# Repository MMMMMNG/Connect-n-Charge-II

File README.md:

# ip12-22vt_ladestationen
FHNW Computer Science Student Project Semester 1&2

# Connect 'n Charge
 <br />

Connect 'n Charge ist ein strategisches Brettspiel, bei dem die Spieler dazu aufgefordert werden, Netzwerkverbindungen zu verknüpfen und dabei Ressourceneffizienz zu optimieren.
Die Spieler übernehmen die Rolle des Managers einer idyllischen Feriensiedlung mit 30 Ferienhäusern, die dazu beitragen sollen, umweltfreundliche Mobilität zu fördern, indem 13 Häuser mit modernen E-Ladestationen ausgestattet werden.
Die Herausforderung liegt dabei in der optimalen Nutzung von Ressourcen und der Schaffung eines effizienten Verteilungsnetzes.

## Setup in IntelliJ IDEA
This repo on GitHub is a fusion of the code and docu repositories, which is why it's a bit tricky to open it as a maven project in Intellij IDEA:

1. Open the repository folder (parent folder of the docu and connectncharge folders)
1. Quickly press shift twice
1. In the popup window, search `Add Maven Projects`

4. Select the folder containing the pom.xml file (`connectncharge/`)
4. To test it, execute a maven goal like `package` in the maven sidebar on the right-hand-side. It should try to build the project.

## Verwendete Hardware

Die folgende Liste zeigt alle Hardware-Komponenten, die im "Connect 'n Charge" Spiel verwendet werden.

Die meisten dieser Komponenten sind leicht in Elektronikfachgeschäften oder online erhältlich.
Achten Sie darauf, die entsprechenden Datasheets und Spezifikationen zu überprüfen, um sicherzustellen, dass Sie die richtigen Teile kaufen.

Ausserdem ist es wichtig zu beachten, dass einige dieser Teile verschleissen können, insbesondere die Taster und die LED-Streifen. Es ist daher ratsam, einige Ersatzteile zur Hand zu haben.
- **Raspberry Pi Modell B:** Dies ist das Herzstück des Spiels, das die gesamte Verarbeitung und Steuerung übernimmt.
- **RaspberryPi-Display 7":** Ein 7-Zoll-Touchscreen-Display, das zur Anzeige von Informationen und zur Interaktion mit dem Spiel verwendet wird.
- **LED-Strip (WS2812b, White PCB, 60LED/m):** Dieser wird verwendet, um den Status der einzelnen Knotenpunkte visuell darzustellen.
- **Schaltnetzteil (DC 5V 20A 100W):** Dieses versorgt das gesamte System mit Strom.
- **TACT SWITCH, 12 x 12mm, 4PIN/THT:** Diese werden als Taster für die Interaktion mit dem Spiel verwendet.
- **Flachbandkabel und Flachbandstecker/-sockel:** Diese werden für die Verbindungen zwischen den verschiedenen Komponenten verwendet.
- **Europlatinen:** Auf diesen werden die Taster montiert.
- **GPIO-Extension-ICs (MCP23S17):** Diese werden verwendet, um mehr GPIO-Pins für den Raspberry Pi bereitzustellen.
- **IC-Sockel:** Diese werden verwendet, um die ICs auf den Platinen zu montieren.
- **Lüfter für Kühlung:** Diese werden verwendet, um das System kühl zu halten.
- **Logic level converter IC (3.3V zu 5V, SN74HCT125):** Dieser wird verwendet, um die Logikpegel zwischen den verschiedenen Komponenten zu konvertieren.
- **Platine mit Audio-Verstärker-IC (TDA2030A AMP 6-12V 1*18W):** Diese wird verwendet, um Audioausgabe zu ermöglichen.
- **Gerätebuchse und Gerätesteckerkabel:** Diese werden für die Stromversorgung des Systems verwendet.

Weitere technische Informationen finden Sie in der Hardware Doku unter folgendem [link](docu/hardware/Hardware.adoc).

## Spiel starten und parametrisieren

### Automatischer Start

"Connect 'n Charge" ist so konzipiert, dass es automatisch startet, sobald es mit Strom versorgt wird.
Dies wird durch ein Autostart-Skript auf dem RaspberryPi ermöglicht.
Das Skript sorgt dafür, dass die notwendige Software geladen und ausgeführt wird, sobald das Gerät mit Strom versorgt wird.

### Betriebsanleitung

"Connect 'n Charge" ist ein einfaches "Plug and Play"-Spiel.
Folgen Sie diesen einfachen Schritten, um das Spiel zu starten:

1. Platzieren Sie das Brettspiel auf einer stabilen und ebenen Oberfläche, z.B. einem Tisch.
2. Schliessen Sie das Stromkabel des Brettspiels an eine Steckdose an.
3. Sobald das Spiel mit Strom versorgt ist, startet es automatisch und befindet sich auf der "Loading-Page".

Bitte beachten Sie, dass das Spiel nur mit einer stabilen Stromversorgung einwandfrei funktioniert.
Stellen Sie sicher, dass die Stromversorgung während des Spielbetriebs nicht unterbrochen wird, um eine Unterbrechung oder Verzögerung im Spielverlauf zu vermeiden.

Für technischere Informationen und Details zum Deployment im Entwicklungs-Umfeld, zur Datenmigration und zur Installation auf neuer Hardware, verweisen wir auf das zugehörige Handbuch.
[Handbuch](docu/Handbuch-ConnectnCharge.pdf)

## Übersetzungen

Unser Spiel "Connect 'n Charge" ist derzeit nur auf Deutsch verfügbar.
Wenn Sie daran interessiert sind, das Spiel in andere Sprachen zu übersetzen, finden Sie die meisten Texte in den XML-Dateien unserer JavaFXML-Screens.

Um die Texte für die Übersetzung zu bearbeiten, gehen Sie folgendermassen vor:

1. Öffnen Sie die entsprechenden XML-Dateien der JavaFXML-Screens.
2. Suchen Sie nach den Textelementen, die übersetzt werden sollen.
3. Ersetzen Sie den deutschen Text durch die gewünschte Übersetzung.

Bitte beachten Sie, dass einige Wörter möglicherweise auch im Java-Code selbst eingebettet sind.
Diese Fälle sind jedoch selten und die Mehrheit der zu übersetzenden Texte finden Sie in den XML-Dateien.

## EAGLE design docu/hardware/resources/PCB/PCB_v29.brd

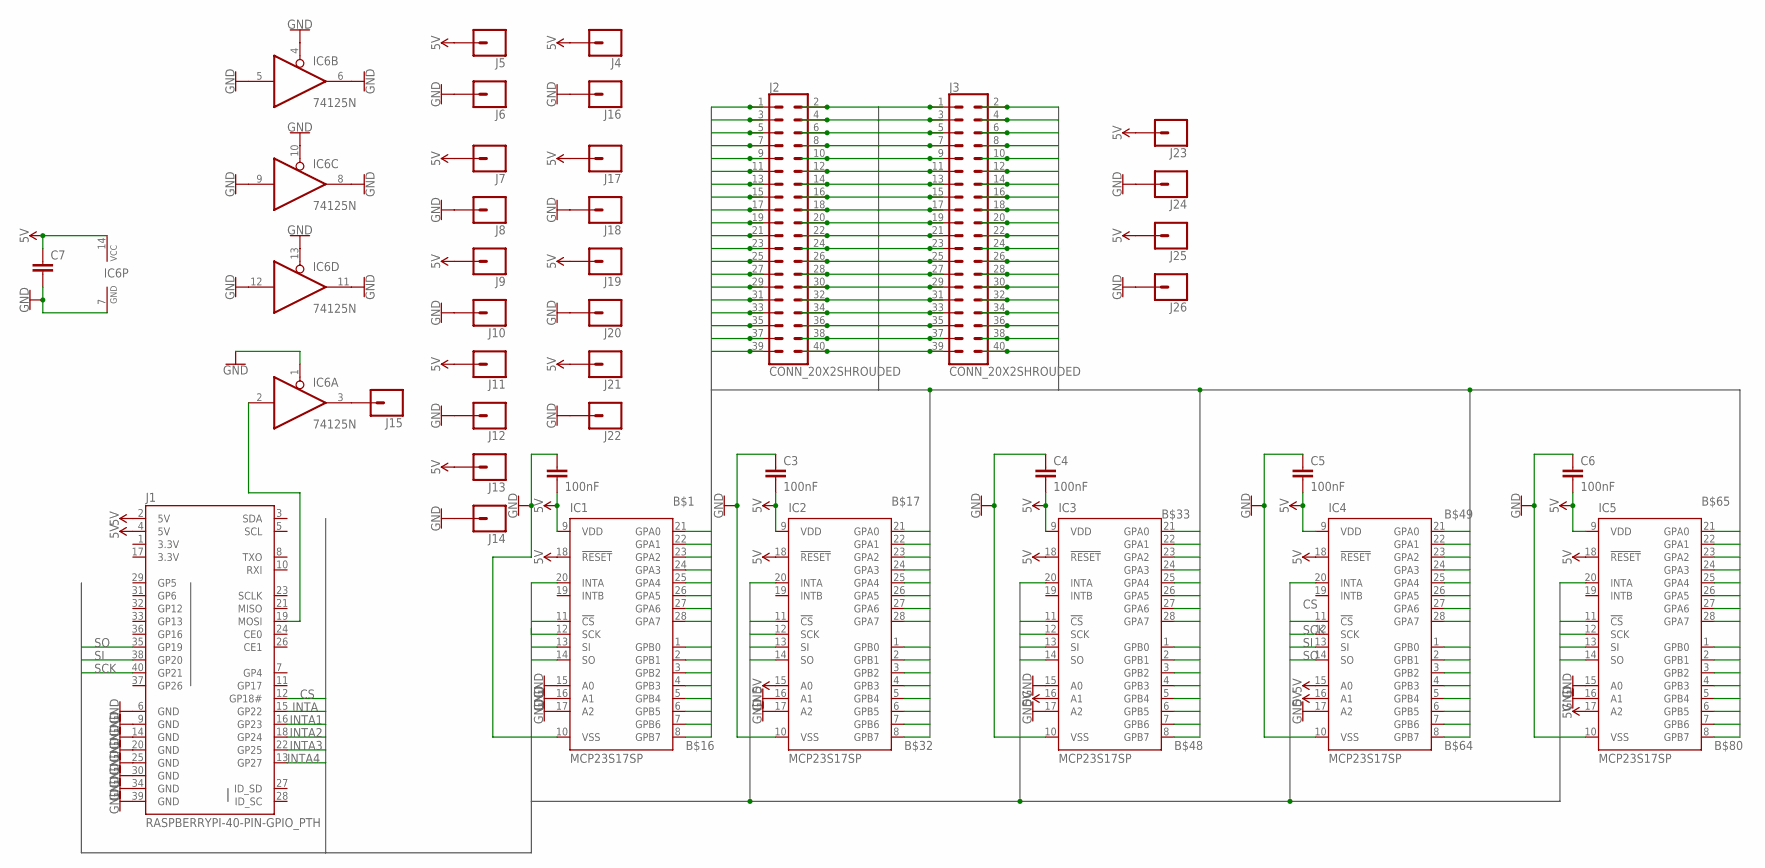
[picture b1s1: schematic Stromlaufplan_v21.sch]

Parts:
C2, C3, C4, C5, C6, C7: 100nF; 0805
IC1, IC2, IC3, IC4, IC5: MCP23S17SP; DIL28-3
IC6: 74125N; DIL14
J1: RASPBERRYPI-40-PIN-GPIO_PTH; 2X20_SHROUDED
J2, J3: CONN_20X2SHROUDED; 2X20_SHROUDED
J4, J7, J8, J9, J10, J11, J12, J13, J14, J15, J16, J17, J18, J19, J20, J21, J22, J23, J24, J25, J26: CONN_01PTH_NO_SILK_YES_STOP; 1X01_NO_SILK
J5, J6: CONN_01; 1X01

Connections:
3.3V: J1.1 (3.3V), J1.17 (3.3V)
5V: C2.2, C3.2, C4.2, C5.2, C6.2, C7.1, IC1.9 (VDD), IC1.18 (!RESET), IC2.9 (VDD), IC2.15 (A0), IC2.18 (!RESET), IC3.9 (VDD), IC3.16 (A1), IC3.18 (!RESET), IC4.9 (VDD), IC4.15 (A0), IC4.16 (A1), IC4.18 (!RESET), IC5.9 (VDD), IC5.17 (A2), IC5.18 (!RESET), IC6.14 (VCC), J1.2 (5V), J1.4 (5V), J4.1, J5.1, J7.1, J9.1, J11.1, J13.1, J17.1, J19.1, J21.1, J23.1, J25.1
B$1: IC1.21 (GPA0), J2.1
B$2: IC1.22 (GPA1), J2.2
B$3: IC1.23 (GPA2), J2.3
B$4: IC1.24 (GPA3), J2.4
B$5: IC1.25 (GPA4), J2.5
B$6: IC1.26 (GPA5), J2.6
B$7: IC1.27 (GPA6), J2.7
B$8: IC1.28 (GPA7), J2.8
B$9: IC1.1 (GPB0), J2.9
B$10: IC1.2 (GPB1), J2.10
B$11: IC1.3 (GPB2), J2.11
B$12: IC1.4 (GPB3), J2.12
B$13: IC1.5 (GPB4), J2.13
B$14: IC1.6 (GPB5), J2.14
B$15: IC1.7 (GPB6), J2.15
B$16: IC1.8 (GPB7), J2.16
B$17: IC2.21 (GPA0), J2.17
B$18: IC2.22 (GPA1), J2.18
B$19: IC2.23 (GPA2), J2.19
B$20: IC2.24 (GPA3), J2.20
B$21: IC2.25 (GPA4), J2.21
B$22: IC2.26 (GPA5), J2.22
B$23: IC2.27 (GPA6), J2.23
B$24: IC2.28 (GPA7), J2.24
B$25: IC2.1 (GPB0), J2.25
B$26: IC2.2 (GPB1), J2.26
B$27: IC2.3 (GPB2), J2.27
B$28: IC2.4 (GPB3), J2.28
B$29: IC2.5 (GPB4), J2.29
B$30: IC2.6 (GPB5), J2.30
B$31: IC2.7 (GPB6), J2.31
B$32: IC2.8 (GPB7), J2.32
B$33: IC3.21 (GPA0), J2.33
B$34: IC3.22 (GPA1), J2.34
B$35: IC3.23 (GPA2), J2.35
B$36: IC3.24 (GPA3), J2.36
B$37: IC3.25 (GPA4), J2.37
B$38: IC3.26 (GPA5), J2.38
B$39: IC3.27 (GPA6), J2.39
B$40: IC3.28 (GPA7), J2.40
B$41: IC3.1 (GPB0), J3.1
B$42: IC3.2 (GPB1), J3.2
B$43: IC3.3 (GPB2), J3.3
B$44: IC3.4 (GPB3), J3.4
B$45: IC3.5 (GPB4), J3.5
B$46: IC3.6 (GPB5), J3.6
B$47: IC3.7 (GPB6), J3.7
B$48: IC3.8 (GPB7), J3.8
B$49: IC4.21 (GPA0), J3.9
B$50: IC4.22 (GPA1), J3.10
B$51: IC4.23 (GPA2), J3.11
B$52: IC4.24 (GPA3), J3.12
B$53: IC4.25 (GPA4), J3.13
B$54: IC4.26 (GPA5), J3.14
B$55: IC4.27 (GPA6), J3.15
B$56: IC4.28 (GPA7), J3.16
B$57: IC4.1 (GPB0), J3.17
B$58: IC4.2 (GPB1), J3.18
B$59: IC4.3 (GPB2), J3.19
B$60: IC4.4 (GPB3), J3.20
B$61: IC4.5 (GPB4), J3.21
B$62: IC4.6 (GPB5), J3.22
B$63: IC4.7 (GPB6), J3.23
B$64: IC4.8 (GPB7), J3.24
B$65: IC5.21 (GPA0), J3.25
B$66: IC5.22 (GPA1), J3.26
B$67: IC5.23 (GPA2), J3.27
B$68: IC5.24 (GPA3), J3.28
B$69: IC5.25 (GPA4), J3.29
B$70: IC5.26 (GPA5), J3.30
B$71: IC5.27 (GPA6), J3.31
B$72: IC5.28 (GPA7), J3.32
B$73: IC5.1 (GPB0), J3.33
B$74: IC5.2 (GPB1), J3.34
B$75: IC5.3 (GPB2), J3.35
B$76: IC5.4 (GPB3), J3.36
B$77: IC5.5 (GPB4), J3.37
B$78: IC5.6 (GPB5), J3.38
B$79: IC5.7 (GPB6), J3.39
B$80: IC5.8 (GPB7), J3.40
CS: IC1.11 (!CS), IC2.11 (!CS), IC3.11 (!CS), IC4.11 (!CS), IC5.11 (!CS), J1.12 (GP18#)
GND: C2.1, C3.1, C4.1, C5.1, C6.1, C7.2, IC1.10 (VSS), IC1.15 (A0), IC1.16 (A1), IC1.17 (A2), IC2.10 (VSS), IC2.16 (A1), IC2.17 (A2), IC3.10 (VSS), IC3.15 (A0), IC3.17 (A2), IC4.10 (VSS), IC4.17 (A2), IC5.10 (VSS), IC5.15 (A0), IC5.16 (A1), IC6.1 (OE), IC6.4 (OE), IC6.5 (I), IC6.6 (O), IC6.7 (GND), IC6.8 (O), IC6.9 (I), IC6.10 (OE), IC6.11 (O), IC6.12 (I), IC6.13 (OE), J1.6 (GND), J1.9 (GND), J1.14 (GND), J1.20 (GND), J1.25 (GND), J1.30 (GND), J1.34 (GND), J1.39 (GND), J6.1, J8.1, J10.1, J12.1, J14.1, J16.1, J18.1, J20.1, J22.1, J24.1, J26.1
INTA: IC1.20 (INTA), J1.15 (GP22)
INTA1: IC2.20 (INTA), J1.16 (GP23)
INTA2: IC3.20 (INTA), J1.18 (GP24)
INTA3: IC4.20 (INTA), J1.22 (GP25)
INTA4: IC5.20 (INTA), J1.13 (GP27)
unnamed: IC6.2 (I), J1.19 (MOSI)
unnamed: IC6.3 (O), J15.1
SCK: IC1.12 (SCK), IC2.12 (SCK), IC3.12 (SCK), IC4.12 (SCK), IC5.12 (SCK), J1.40 (GP21)
SI: IC1.13 (SI), IC2.13 (SI), IC3.13 (SI), IC4.13 (SI), IC5.13 (SI), J1.38 (GP20)
SO: IC1.14 (SO), IC2.14 (SO), IC3.14 (SO), IC4.14 (SO), IC5.14 (SO), J1.35 (GP19)

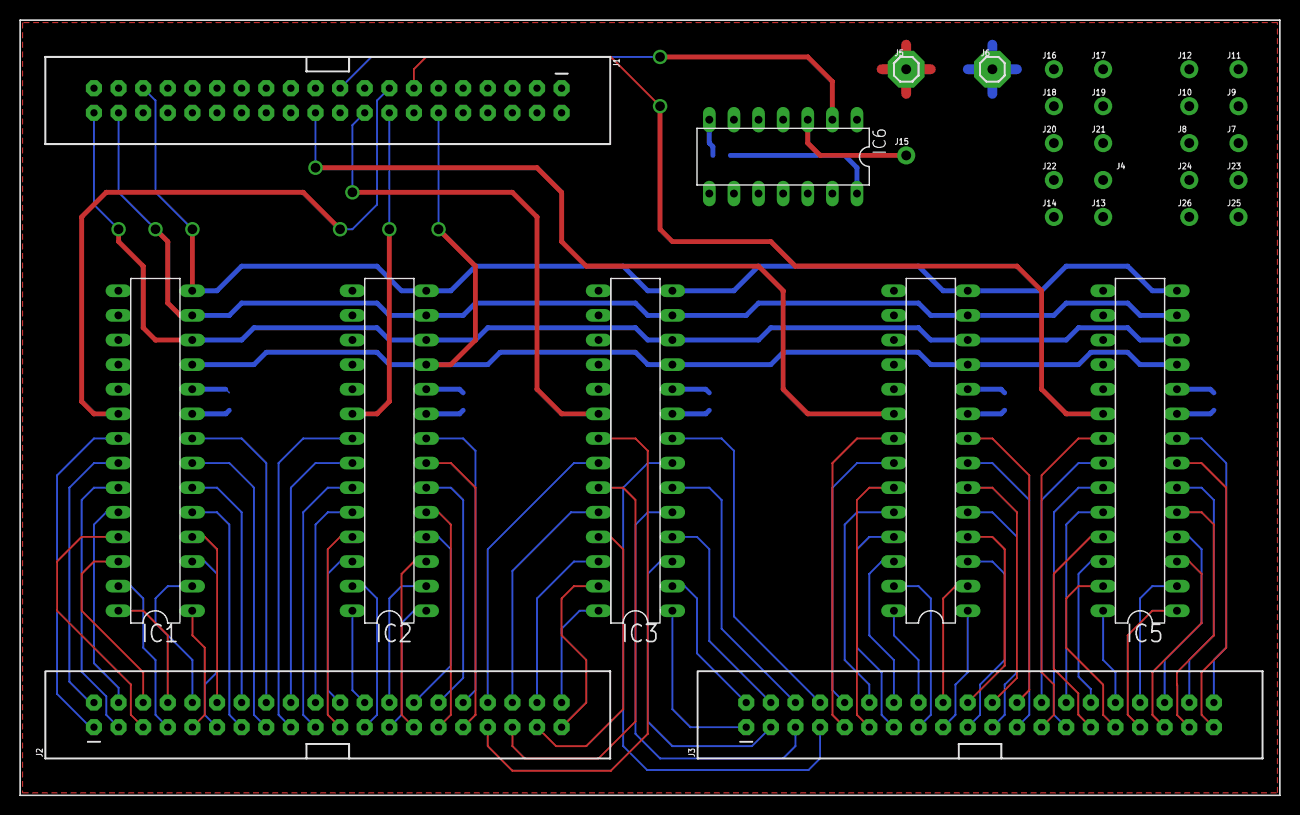
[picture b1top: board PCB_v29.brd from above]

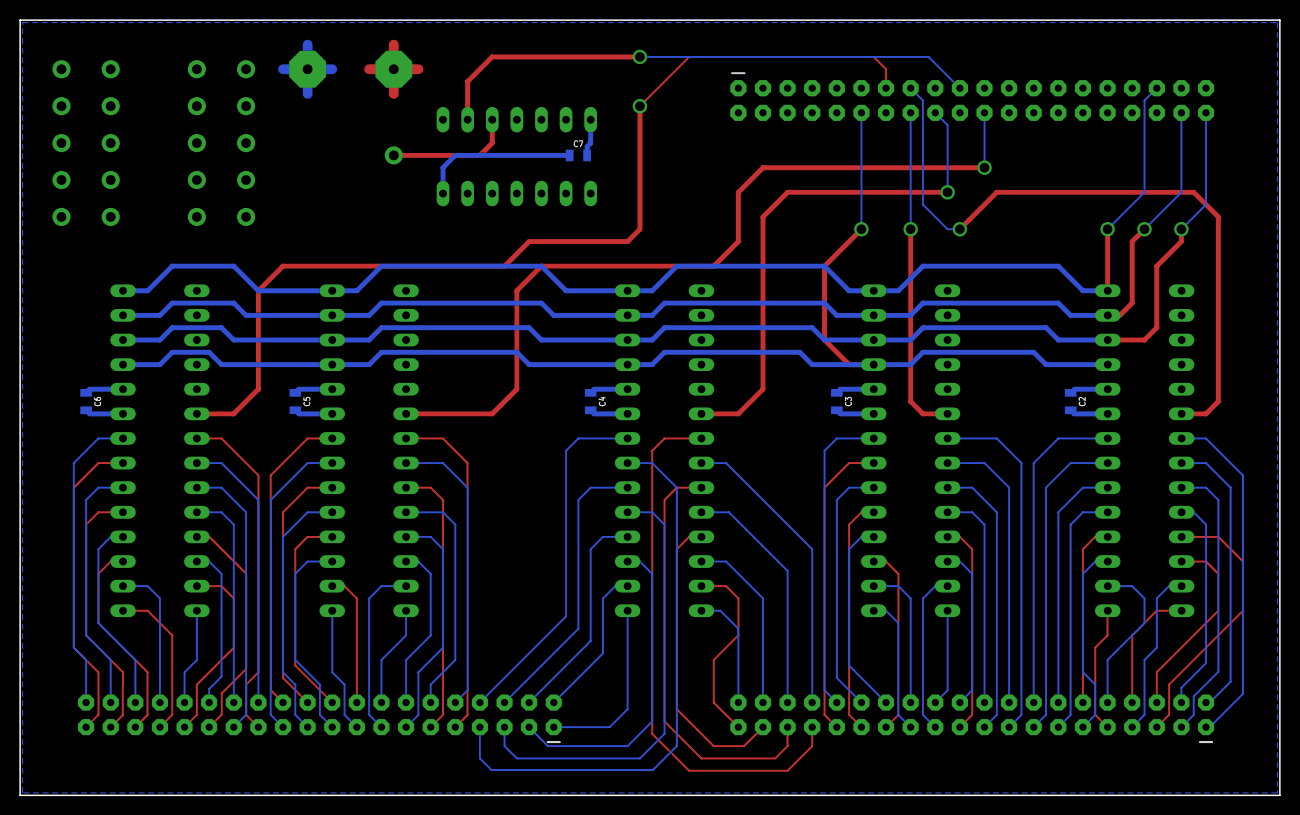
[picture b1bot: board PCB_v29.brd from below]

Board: 2 copper layers, 130.0 x 80.0 mm, 38 parts (6 on the bottom side), 94 nets.

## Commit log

2023-08-17 another try to get the inconsistent test results under control.
2023-08-18 Update README.md
    changed badges and added relevant links
2023-08-25 using color of hint enum instead of hardcoded color
    and change color in hint enum to red.
2023-08-25 changing logger pattern and detail
2023-08-25 contain checked exception
    instead of propagating it up the method chain
2023-08-25 add getter for all edges
2023-08-25 make Edge.isOn dependent on Game.activatedEdges
    It is done in the constructor of Game(). That way these two "sources of truth" are synced.
2023-08-25 add a bunch of log statements
    as well as synchronized keywords in ConcurrentTaskQueue.java
2023-08-25 add a bunch tests for the ApplicationController
    finally pushing the coverage of ApplicationController to 100%
2023-08-25 remove unnecessary try catch blocks
    also add a few log statements and remove now redundant calls to Edge.on() & Edge.off()
2023-08-25 add utility methods for adding and removing elements from ObservableArrays
    This finally uses the intended async functionality that probably makes it testable. This calls for a major refactoring. I assume most of the consistency issues when testing came from using outdated v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
2023-08-25 refactor ApplicationController and ApplicationControllerTest
2023-08-25 remove commented out line
2023-08-25 exclude classes that aren't being tested in this project from report
    easiest way to bump up coverage ;). JavaFX classes have been excluded too, it might be worth testing these in the future with TestFX for example.
2023-08-27 add synchronous counterparts for most of the setter methods
2023-08-27 make use of the synchronous setter methods to eliminate controller.awaitCompletion() inconsistencies
    The problem was that actions scheduled for async execution with the async() function (like setValue()) would themselves cause scheduling of async actions FROM the async context (this would introduce 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
2023-08-27 improve the logging significantly
    Now every state-change is logged from the Game class (the model) in a nice, clean manner.
2023-09-17 adds all the necessary config files for the Pi
    ...like the auto start service, WLAN and SPI-config
2023-09-17 makes the pom use the correct version of the antrun plugin explicitly
2023-09-17 first functional version, but with wrong Button-to-Edge-Associations
2023-09-17 functional version with correct Button-to-Edge-associations
2023-09-17 fixes missing Button-Chip-Edge associations
2023-09-17 adds Animation infrastructure
2023-09-17 adds working Animation implementations
2023-09-22 add win and notification sounds, move sound code to pui
2023-09-22 configure taskbar to be hidden
2023-09-22 fixed faulty removal of element during list traversal
2023-09-22 fix handling of edges with even and uneven LED amounts
2023-09-22 makes highscore work
    also fixes bugs, refactors and adds a test.
2023-10-12 implement mute button in side-menu
    horrible bug: muting influences animations.
2023-10-12 refactor Segment.isOn() function to look up state in Game.activatedEdges and Game.terminals
    This hopefully fixes the nasty bug where LED-anims completely break if the game is muted (first of all ???, second of all: the Segment.isOn() function was used to check if an anim should be aborted. 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
2023-10-13 hide all occurences of bonus round
    This feature went out of scope during development pretty quickly
2023-10-13 fix bug where pressing the blinking edge immediately starts countdown from homepage
    state wasn't correctly being reset (this is why having so many state variables in such a spaghetti config sucks)
2023-10-13 fix loose ends where game state becomes broken because unexpected paths are taken through the UI
    🙄
2023-10-13 add credits scene
    (FINALLY!)
2023-10-13 add credits button to side menu
    only @ homepage 'cuz the side menu was made the Spaghetti™ way
2023-10-13 finalize credits
2023-10-13 add credits music
2023-10-13 add Mauro Tammaro to special thanks section
2023-10-13 make side menu initially invisible
2023-10-13 adjust scrolllength a lil' bit

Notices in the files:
parts and their libraries:
SparkFun-Connectors_Ladestation: Licensing: Creative Commons ShareAlike 4.0 International - https://creativecommons.org/licenses/by-sa/4.0
